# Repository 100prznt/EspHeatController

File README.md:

# HeatController
Bang-bang heat controller with 2 channels. ESP8266 based and compatible with Home Assistant.

## Specs
- ESP8266MOD (ESP-12-F)
- Onboard USB-UART bridge (FTDI)
- 230 VAC power supply with higher isolation voltage (for use in wet environment)
- Automatic switching of the power supply between USB and AC power
- Fully compatible with ESPHome and Home Assistant
- 2 output channels (230 VAC max. 10 A)
- 5 header for DS18B20 1-Wire temperature sensors
- Header for analog input

## Assembly
The PCB fits into a [Spelsberg TG PC 1612-9-to](https://www.spelsberg.de/industrieleergehaeuse/glatt-mit-befestigungsnocken/20100701/) enclosure. There is lots of space for the 230 V wiring in the lower area. I have installed PowerCon sockets from Neutrik here and M8 sockets for the DS818B20 sensors.

## Home Assistant

### Dashboard
The initial use of the __EspHeatController__ for me was as a frost watcher in addition to a pipe heating system. I created a separate dashboard in Home Assistant for this use case.

You can find the configuration for this dashboard here:

* [dashboard/lovelace_ehc_config.yaml](dashboard/lovelace_ehc_config.yaml)

The following HACS extensions are required for this dashboard:

* [Mushroom](https://github.com/piitaya/lovelace-mushroom)
* [UI Card for Better Thermostat](https://github.com/KartoffelToby/better-thermostat-ui-card)

## Usage
As mentioned above, I use the __EspHeatController__ as a frost protector, the ESPHome config [esphome_ehc_config.yaml](esphome_ehc_config.yaml) implements a bang-bang controller for this. Alternatively, the hardware can be configured as a thermostat. It is also possible to control a cooling system in addition to the heater using the two switching channels.

## Function and description

### Datasheets
* [FTDI FT232BL](https://ftdichip.com/wp-content/uploads/2020/08/DS_FT232BL_BQ.pdf)
* [STMicroelectronics LD1117S](http://www.st.com/content/ccc/resource/technical/document/datasheet/99/3b/7d/91/91/51/4b/be/CD00000544.pdf/files/CD00000544.pdf/jcr:content/translations/en.CD00000544.pdf)
* [TI TPS2104](https://www.ti.com/lit/gpn/tps2104)
* [Rohm UMH3N](https://fscdn.rohm.com/en/products/databook/datasheet/discrete/transistor/digital/umh3ntn-e.pdf)
* [AI Thinker ESP8266MOD](https://docs.ai-thinker.com/_media/esp8266/docs/esp-12f_product_specification_en.pdf)

## Hardware Versions
See [versions.md](versions.md) for hardware version details.

### Known bugs in HW rev. v1.0
* [ ] Different resistor packages (R0603 vs. R0805W)
* [ ] IC301 invalide function table for USB power only
* [ ] IC300 (LD1117S) thermal != gnd
* [ ] IC200 (FT232BL) logiclevel for RST pin must be 5 V

### Features for next version
Features for new hardware versions.

* [ ] Onboard temperature sensor
* [ ] X202: Use stadard FTDI header pin assigment ([Datasheet TTL-232R](https://ftdichip.com/wp-content/uploads/2023/07/DS_TTL-232R_CABLES.pdf))
* [ ] Hardware lock between both relays (to use as 2-way motor switch)
* [ ] Hardware lock for the relays in boot state (check an [IO expander](https://esphome.io/#miscellaneous-components))
* [ ] Expand space between PE and GND
* [ ] Testpins for 5 V power supply
* [ ] Change FT232BL to [FT232RNL](https://ftdichip.com/wp-content/uploads/2023/03/DS_FT232RN.pdf) or external programmer

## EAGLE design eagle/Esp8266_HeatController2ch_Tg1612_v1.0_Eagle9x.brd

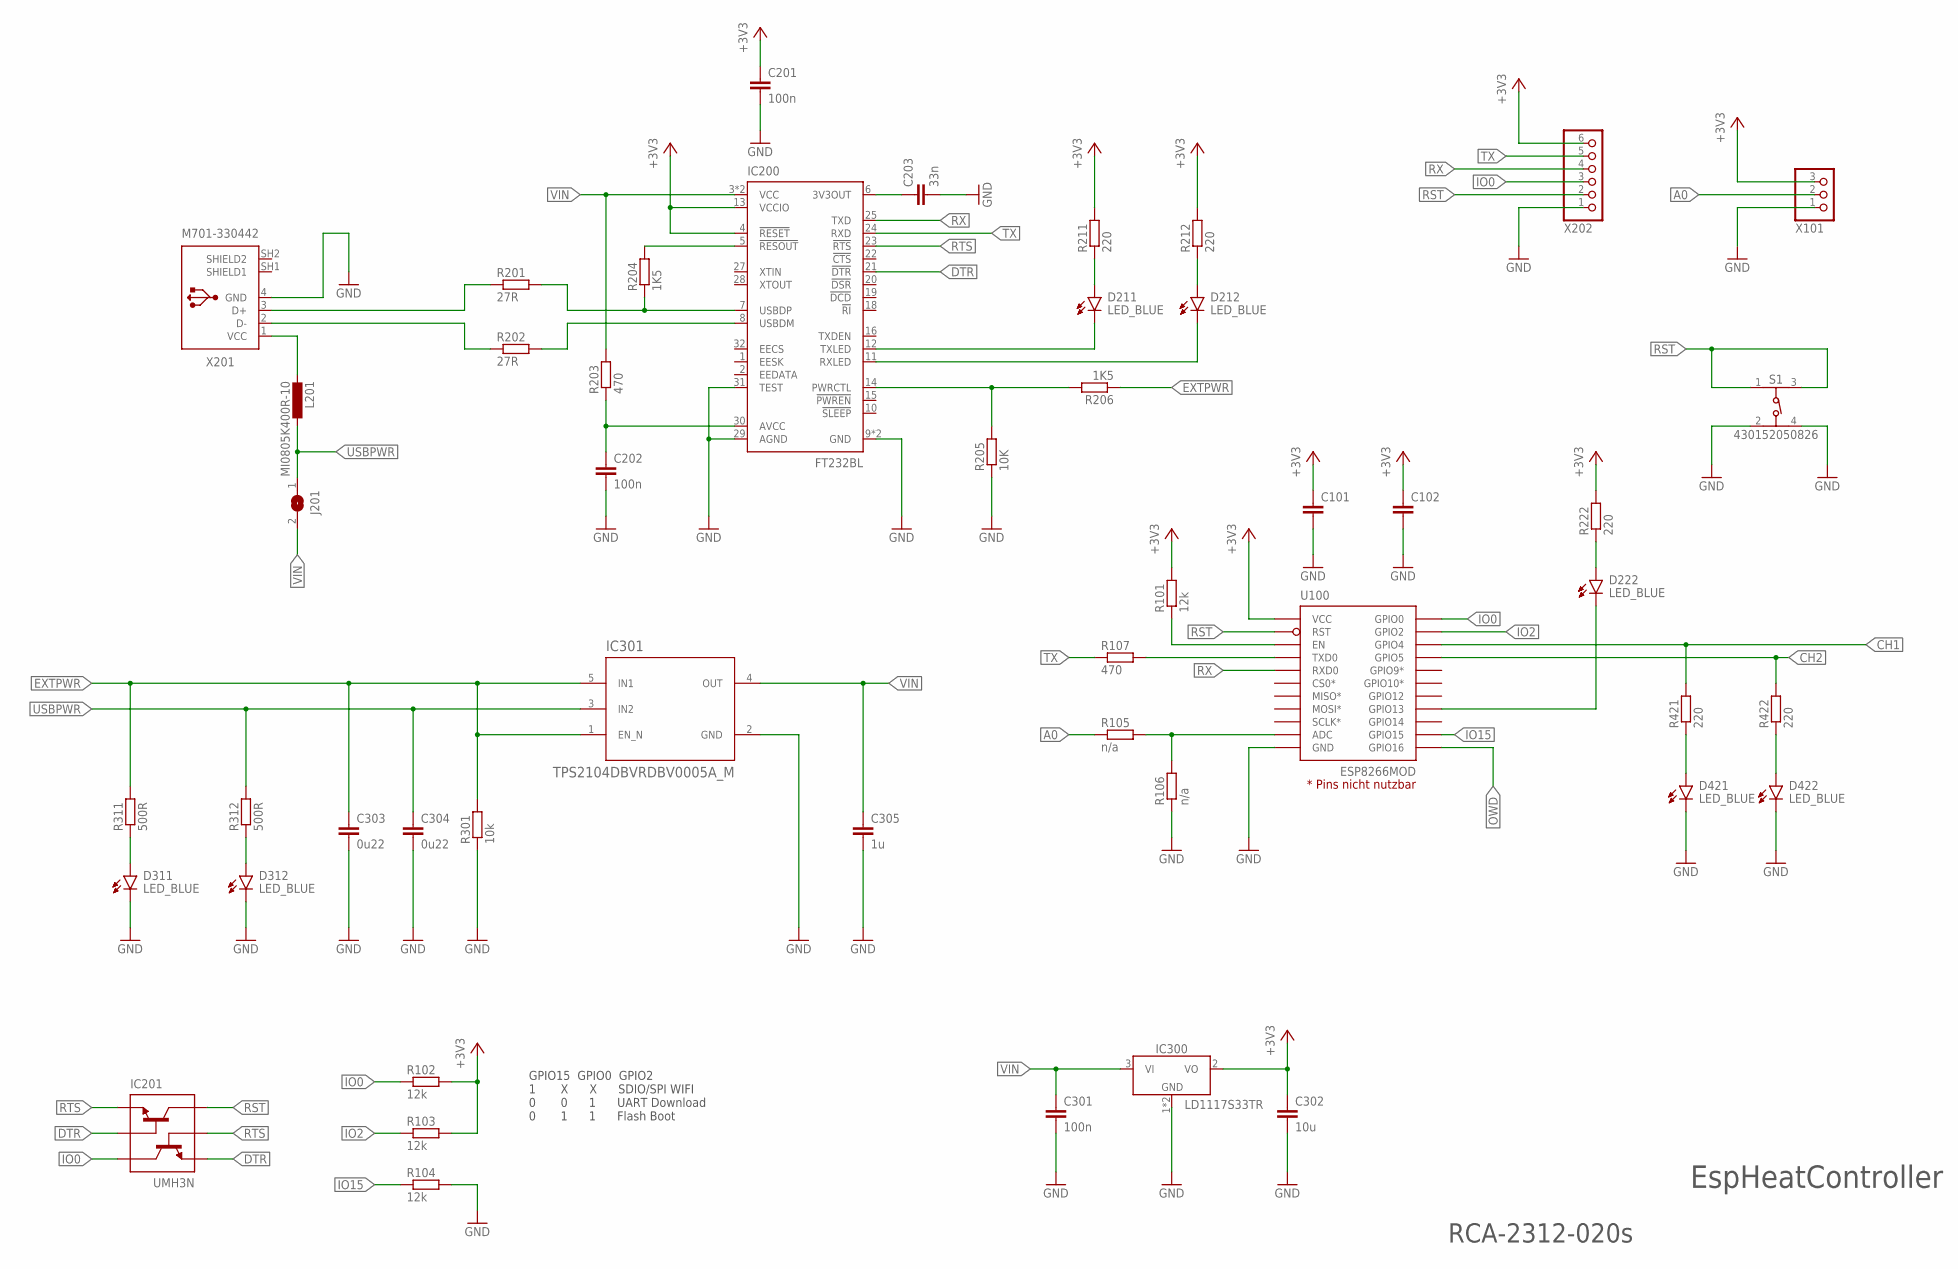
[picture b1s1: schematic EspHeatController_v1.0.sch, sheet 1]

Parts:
C101, C102: C-EUC0805; C0805
C201, C202, C301: 100n; C0805
C203: 33n; C0805
C302: 10u; C0805
C303, C304: 0u22; C0805
C305: 1u; C0805
D211, D212, D222, D311, D312, D421, D422: LED_BLUE; LEDC2012X110N_FLAT-B
IC200: FT232BL; LQFP32-7X7
IC201: UMH3N; SOT-363_ROM
IC300: LD1117S33TR; SOT230P700X170-4
IC301: TPS2104DBVRDBV0005A_M; DBV0005A_M
J201: SJ
L201: MI0805K400R-10; L2012C
R101, R102, R103, R104: 12k; R0603
R105, R106: n/a; R0603
R107, R203: 470; R0603
R201, R202: 27R; R0603
R204, R206: 1K5; R0603
R205: 10K; R0603
R211, R212, R222, R421, R422: 220; R0603
R301: 10k; R0603
R311, R312: 500R; R0603
S1: 430152050826
U100: ESP8266MOD; ESP12F-SMD
X101: PINHD-1X3; 1X03
X201: M701-330442
X202: PINHD-1X6; 1X06

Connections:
+3V3: C101.1, C102.1, C201.1, C302.1, IC200.4 (!RESET), IC200.13 (VCCIO), IC300.2 (VO), R101.2, R102.2, R103.2, R211.2, R212.2, R222.2, U100.VCC, X101.3, X202.6; also elsewhere on the board
A0: R105.1, X101.2
CH1: R421.2, U100.GPIO4; also elsewhere on the board
CH2: R422.2, U100.GPIO5; also elsewhere on the board
DTR: IC200.21 (!DTR), IC201.2 (B1), IC201.4 (E2)
D_N: IC200.8 (USBDM), R202.2
D_P: IC200.7 (USBDP), R201.2, R204.1
EXTPWR: C303.1, IC301.1 (EN_N), IC301.5 (IN1), R206.1, R301.2, R311.2; also elsewhere on the board
GND: C101.2, C102.2, C201.2, C202.2, C203.2, C301.2, C302.2, C303.2, C304.2, C305.2, D311.C, D312.C, D421.C, D422.C, IC200.9 (GND), IC200.17 (GND), IC200.29 (AGND), IC200.31 (TEST), IC300.1 (GND), IC300.4 (GND), IC301.2 (GND), R104.2, R106.1, R205.1, R301.1, S1.2, S1.4, U100.GND, X101.1, X201.4 (GND), X202.1; also elsewhere on the board
IO0: IC201.3 (C2), R102.1, U100.GPIO0, X202.3
IO2: R103.1, U100.GPIO2
IO15: R104.1, U100.GPIO15
unnamed: R105.2, R106.2, U100.ADC
unnamed: R107.2, U100.TXD0
unnamed: R101.1, U100.EN
unnamed: D211.C, IC200.12 (TXLED)
unnamed: C202.1, IC200.30 (AVCC), R203.1
unnamed: D212.C, IC200.11 (RXLED)
unnamed: D211.A, R211.1
unnamed: D212.A, R212.1
unnamed: C203.1, IC200.6 (3V3OUT)
unnamed: D312.A, R312.1
unnamed: D422.A, R422.1
unnamed: L201.2, X201.1 (VCC)
unnamed: D311.A, R311.1
unnamed: D421.A, R421.1
unnamed: IC200.5 (!RESOUT), R204.2
unnamed: IC200.14 (PWRCTL), R205.2, R206.2
unnamed: D222.C, U100.GPIO13
unnamed: D222.A, R222.1
OWD: U100.GPIO16; also elsewhere on the board
RST: IC201.6 (C1), S1.1, S1.3, U100.RST, X202.2
RTS: IC200.23 (!RTS), IC201.1 (E1), IC201.5 (B2)
RX: IC200.25 (TXD), U100.RXD0, X202.4
TX: IC200.24 (RXD), R107.1, X202.5
USBD_N: R202.1, X201.2 (D-)
USBD_P: R201.1, X201.3 (D+)
USBPWR: C304.1, IC301.3 (IN2), J201.1, L201.1, R312.2
VIN: C301.1, C305.1, IC200.3 (VCC), IC200.26 (VCC), IC300.3 (VI), IC301.4 (OUT), J201.2, R203.2

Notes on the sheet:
GPIO15 GPIO0 GPIO2 1 X X SDIO/SPI WIFI 0 0 1 UART Download 0 1 1 Flash Boot
RCA-2312-020s
EspHeatController

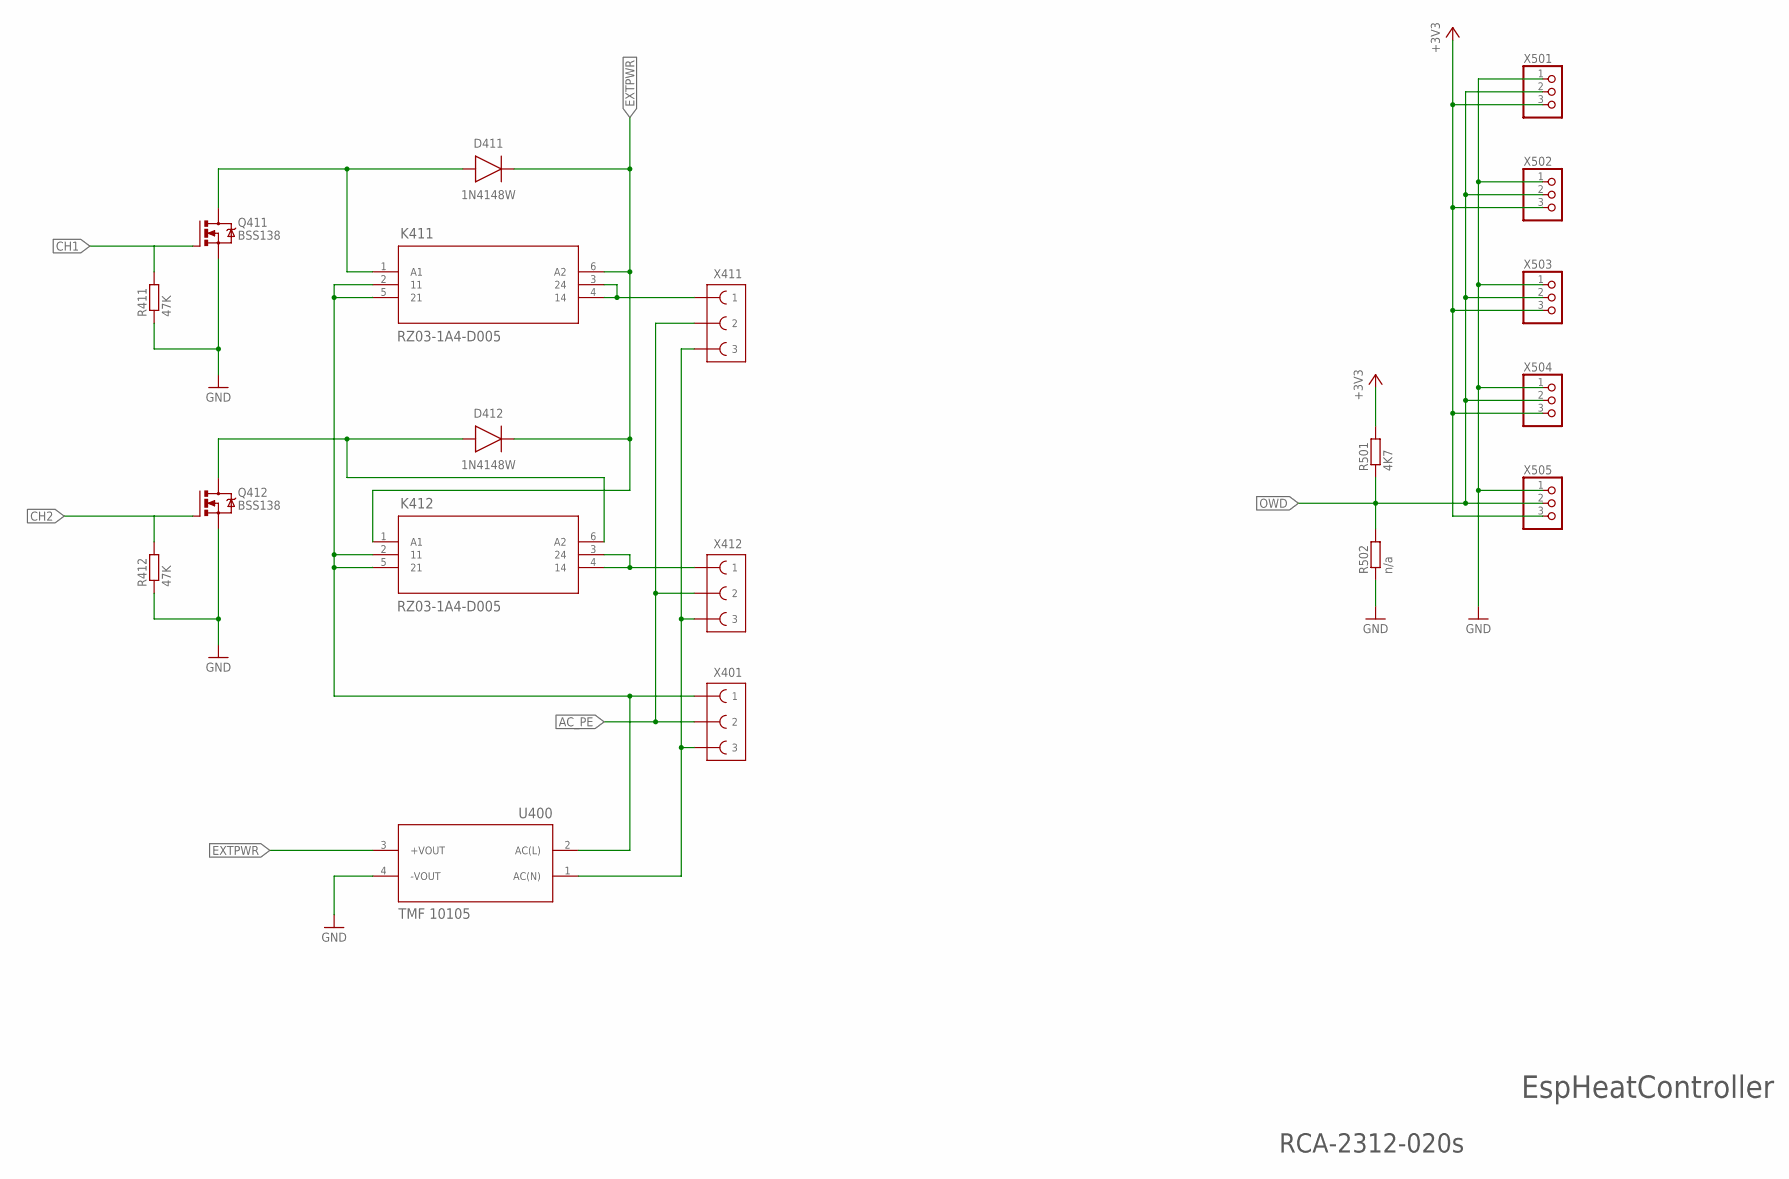
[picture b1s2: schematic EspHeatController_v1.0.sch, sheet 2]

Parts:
D411, D412: 1N4148W; SOD3715X135
K411, K412: RZ03-1A4-D005; RELAY-SPST2_5MM
Q411, Q412: BSS138; SOT23
R411, R412: 47K; R0805W
R501: 4K7; R0805W
R502: n/a; R0805W
U400: TMF 10105; TMF10
X401, X411, X412: SPT2,5/3-V-5,0
X501, X502, X503, X504, X505: PINHD-1X3; 1X03

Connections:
+3V3: R501.2, X501.3, X502.3, X503.3, X504.3, X505.3; also elsewhere on the board
AC_L: K411.2 (11), K411.5 (21), K412.2 (11), K412.5 (21), U400.2 (AC(L)), X401.1A (1), X401.1B (1)
AC_N: U400.1 (AC(N)), X401.3A (3), X401.3B (3), X411.3A (3), X411.3B (3), X412.3A (3), X412.3B (3)
AC_PE: X401.2A (2), X401.2B (2), X411.2A (2), X411.2B (2), X412.2A (2), X412.2B (2)
CH1: Q411.1 (G), R411.2; also elsewhere on the board
CH2: Q412.1 (G), R412.2; also elsewhere on the board
EXTPWR: D411.1 (C), D412.1 (C), K411.6 (A2), K412.1 (A1), U400.3 (+VOUT); also elsewhere on the board
GND: Q411.2 (S), Q412.2 (S), R411.1, R412.1, R502.1, U400.4 (-VOUT), X501.1, X502.1, X503.1, X504.1, X505.1; also elsewhere on the board
unnamed: D412.2 (A), K412.6 (A2), Q412.3 (D)
unnamed: D411.2 (A), K411.1 (A1), Q411.3 (D)
unnamed: K411.3 (24), K411.4 (14), X411.1A (1), X411.1B (1)
unnamed: K412.3 (24), K412.4 (14), X412.1A (1), X412.1B (1)
OWD: R501.1, R502.2, X501.2, X502.2, X503.2, X504.2, X505.2; also elsewhere on the board

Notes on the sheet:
EspHeatController
RCA-2312-020s

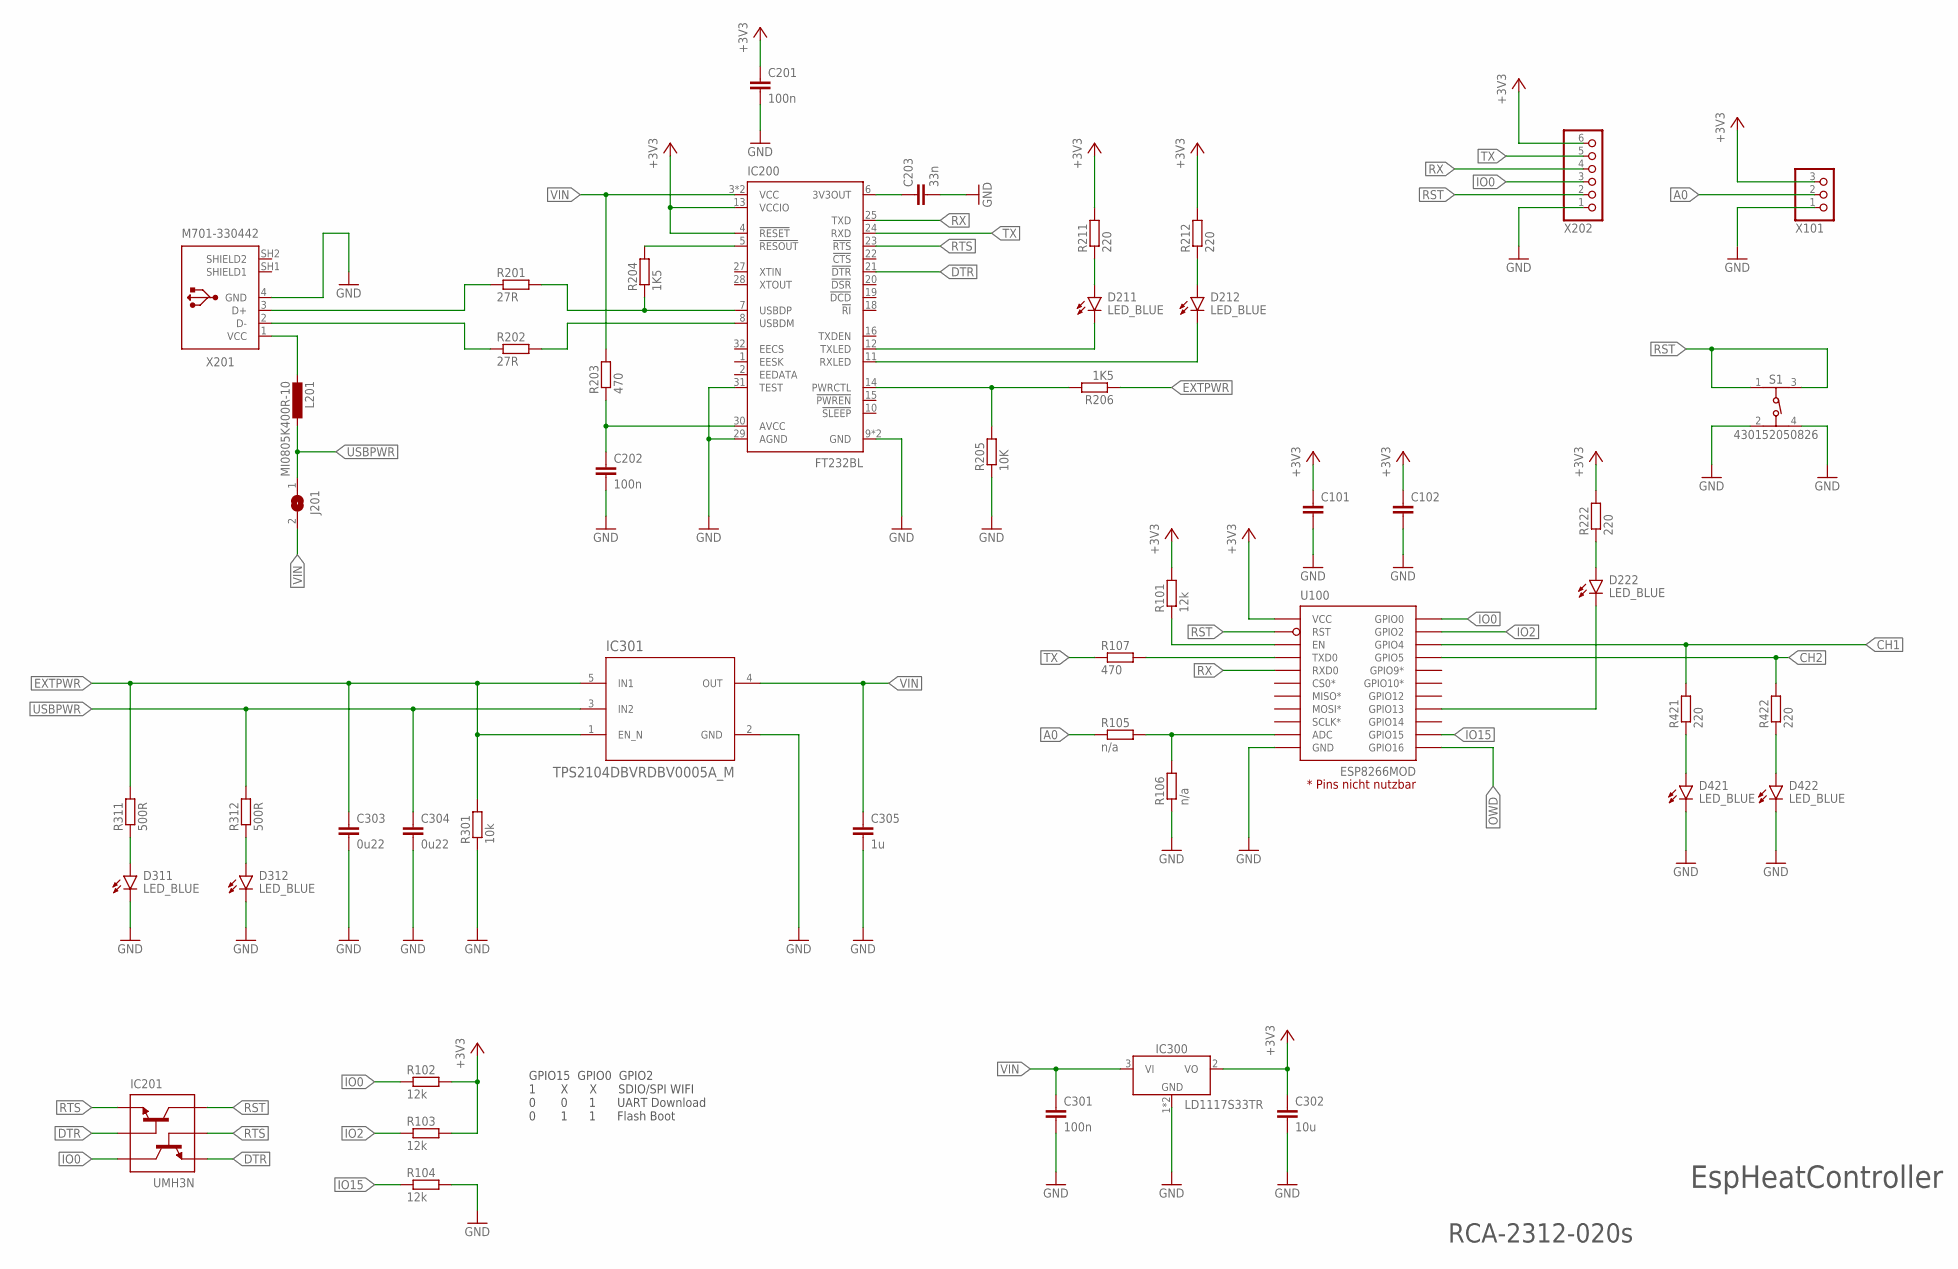
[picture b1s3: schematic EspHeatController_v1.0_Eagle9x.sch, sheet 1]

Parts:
C101, C102: C-EUC0805; C0805
C201, C202, C301: 100n; C0805
C203: 33n; C0805
C302: 10u; C0805
C303, C304: 0u22; C0805
C305: 1u; C0805
D211, D212, D222, D311, D312, D421, D422: LED_BLUE; LEDC2012X110N_FLAT-B
IC200: FT232BL; LQFP32-7X7
IC201: UMH3N; SOT-363_ROM
IC300: LD1117S33TR; SOT230P700X170-4
IC301: TPS2104DBVRDBV0005A_M; DBV0005A_M
J201: SJ
L201: MI0805K400R-10; L2012C
R101, R102, R103, R104: 12k; R0603
R105, R106: n/a; R0603
R107, R203: 470; R0603
R201, R202: 27R; R0603
R204, R206: 1K5; R0603
R205: 10K; R0603
R211, R212, R222, R421, R422: 220; R0603
R301: 10k; R0603
R311, R312: 500R; R0603
S1: 430152050826
U100: ESP8266MOD; ESP12F-SMD
X101: PINHD-1X3; 1X03
X201: M701-330442
X202: PINHD-1X6; 1X06

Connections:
+3V3: C101.1, C102.1, C201.1, C302.1, IC200.4 (!RESET), IC200.13 (VCCIO), IC300.2 (VO), R101.2, R102.2, R103.2, R211.2, R212.2, R222.2, U100.VCC, X101.3, X202.6; also elsewhere on the board
A0: R105.1, X101.2
CH1: R421.2, U100.GPIO4; also elsewhere on the board
CH2: R422.2, U100.GPIO5; also elsewhere on the board
DTR: IC200.21 (!DTR), IC201.2 (B1), IC201.4 (E2)
D_N: IC200.8 (USBDM), R202.2
D_P: IC200.7 (USBDP), R201.2, R204.1
EXTPWR: C303.1, IC301.1 (EN_N), IC301.5 (IN1), R206.1, R301.2, R311.2; also elsewhere on the board
GND: C101.2, C102.2, C201.2, C202.2, C203.2, C301.2, C302.2, C303.2, C304.2, C305.2, D311.C, D312.C, D421.C, D422.C, IC200.9 (GND), IC200.17 (GND), IC200.29 (AGND), IC200.31 (TEST), IC300.1 (GND), IC300.4 (GND), IC301.2 (GND), R104.2, R106.1, R205.1, R301.1, S1.2, S1.4, U100.GND, X101.1, X201.4 (GND), X202.1; also elsewhere on the board
IO0: IC201.3 (C2), R102.1, U100.GPIO0, X202.3
IO2: R103.1, U100.GPIO2
IO15: R104.1, U100.GPIO15
unnamed: R105.2, R106.2, U100.ADC
unnamed: R107.2, U100.TXD0
unnamed: R101.1, U100.EN
unnamed: D211.C, IC200.12 (TXLED)
unnamed: C202.1, IC200.30 (AVCC), R203.1
unnamed: D212.C, IC200.11 (RXLED)
unnamed: D211.A, R211.1
unnamed: D212.A, R212.1
unnamed: C203.1, IC200.6 (3V3OUT)
unnamed: D312.A, R312.1
unnamed: D422.A, R422.1
unnamed: L201.2, X201.1 (VCC)
unnamed: D311.A, R311.1
unnamed: D421.A, R421.1
unnamed: IC200.5 (!RESOUT), R204.2
unnamed: IC200.14 (PWRCTL), R205.2, R206.2
unnamed: D222.C, U100.GPIO13
unnamed: D222.A, R222.1
OWD: U100.GPIO16; also elsewhere on the board
RST: IC201.6 (C1), S1.1, S1.3, U100.RST, X202.2
RTS: IC200.23 (!RTS), IC201.1 (E1), IC201.5 (B2)
RX: IC200.25 (TXD), U100.RXD0, X202.4
TX: IC200.24 (RXD), R107.1, X202.5
USBD_N: R202.1, X201.2 (D-)
USBD_P: R201.1, X201.3 (D+)
USBPWR: C304.1, IC301.3 (IN2), J201.1, L201.1, R312.2
VIN: C301.1, C305.1, IC200.3 (VCC), IC200.26 (VCC), IC300.3 (VI), IC301.4 (OUT), J201.2, R203.2

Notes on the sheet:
GPIO15 GPIO0 GPIO2 1 X X SDIO/SPI WIFI 0 0 1 UART Download 0 1 1 Flash Boot
RCA-2312-020s
EspHeatController

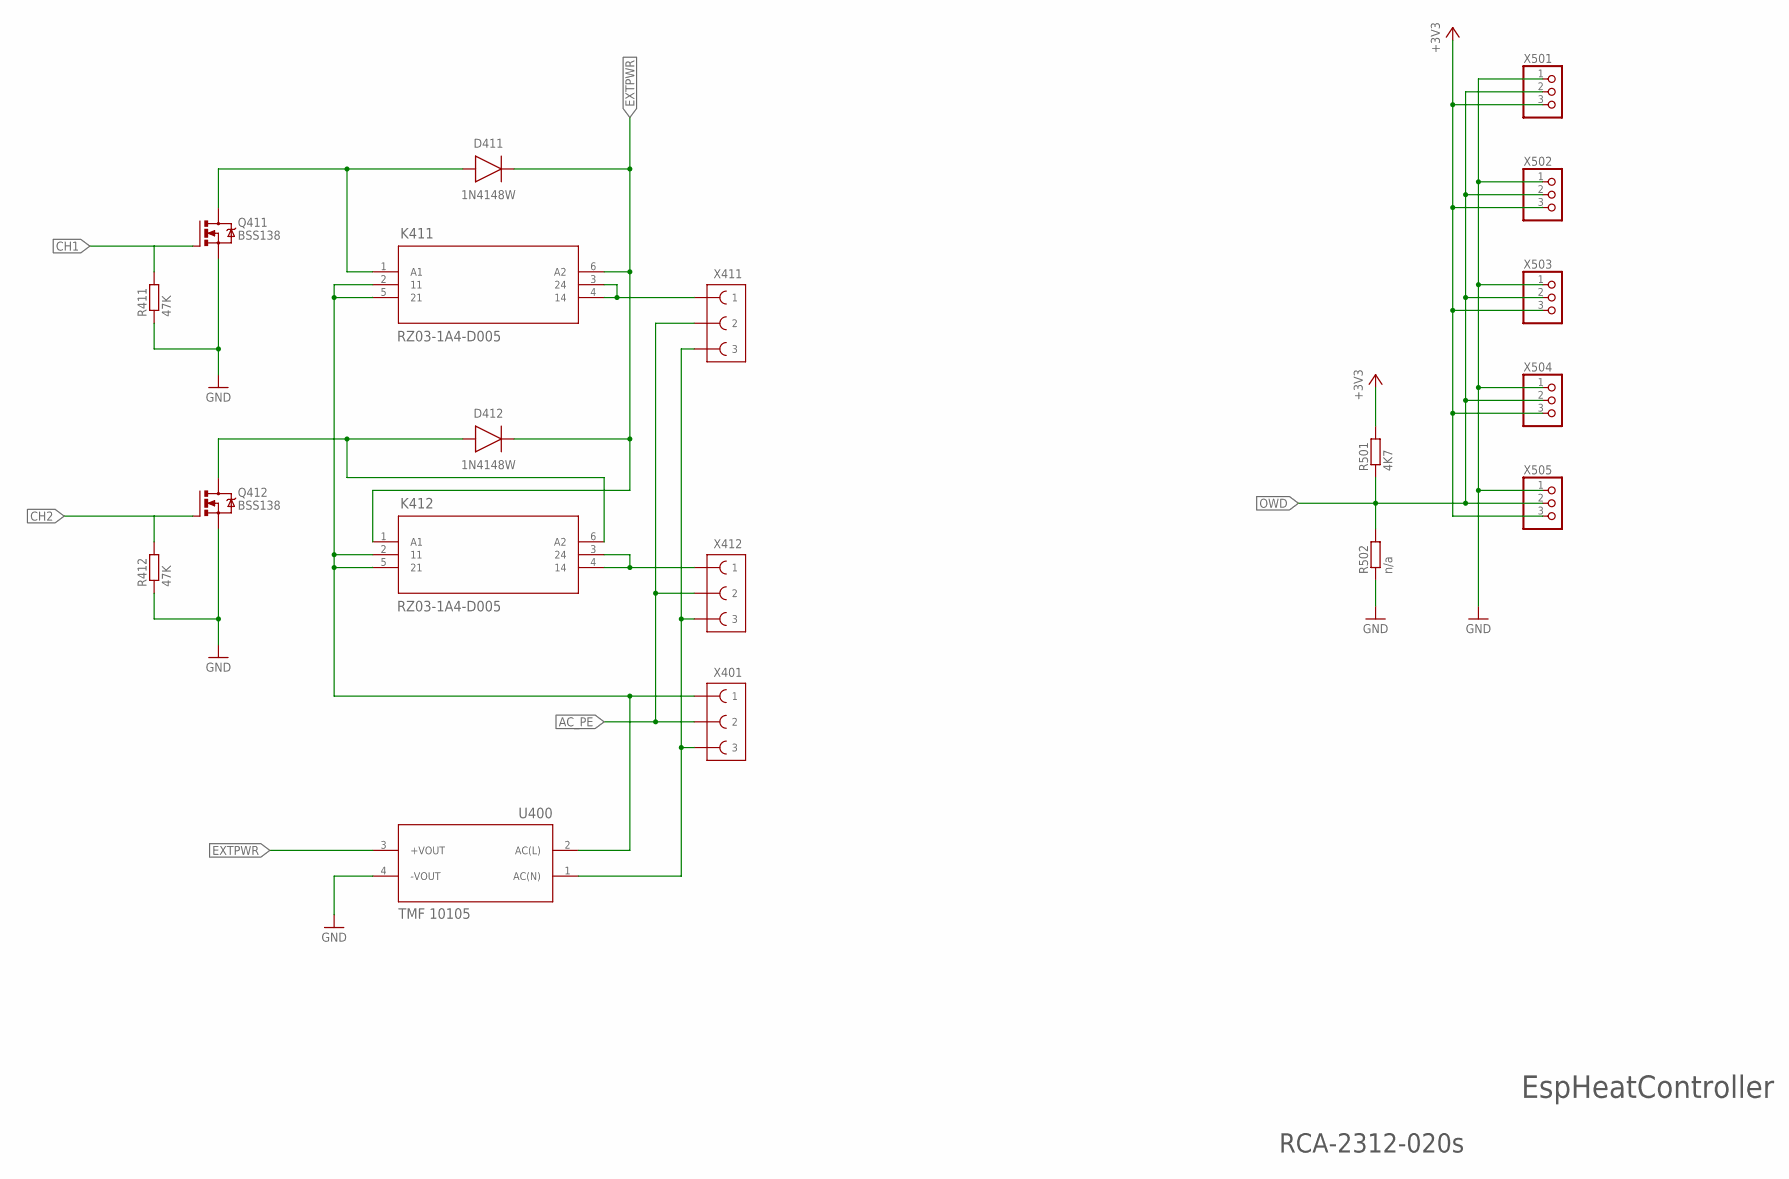
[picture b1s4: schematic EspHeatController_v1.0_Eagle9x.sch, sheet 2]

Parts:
D411, D412: 1N4148W; SOD3715X135
K411, K412: RZ03-1A4-D005; RELAY-SPST2_5MM
Q411, Q412: BSS138; SOT23
R411, R412: 47K; R0805W
R501: 4K7; R0805W
R502: n/a; R0805W
U400: TMF 10105; TMF10
X401, X411, X412: SPT2,5/3-V-5,0
X501, X502, X503, X504, X505: PINHD-1X3; 1X03

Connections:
+3V3: R501.2, X501.3, X502.3, X503.3, X504.3, X505.3; also elsewhere on the board
AC_L: K411.2 (11), K411.5 (21), K412.2 (11), K412.5 (21), U400.2 (AC(L)), X401.1A (1), X401.1B (1)
AC_N: U400.1 (AC(N)), X401.3A (3), X401.3B (3), X411.3A (3), X411.3B (3), X412.3A (3), X412.3B (3)
AC_PE: X401.2A (2), X401.2B (2), X411.2A (2), X411.2B (2), X412.2A (2), X412.2B (2)
CH1: Q411.1 (G), R411.2; also elsewhere on the board
CH2: Q412.1 (G), R412.2; also elsewhere on the board
EXTPWR: D411.1 (C), D412.1 (C), K411.6 (A2), K412.1 (A1), U400.3 (+VOUT); also elsewhere on the board
GND: Q411.2 (S), Q412.2 (S), R411.1, R412.1, R502.1, U400.4 (-VOUT), X501.1, X502.1, X503.1, X504.1, X505.1; also elsewhere on the board
unnamed: D412.2 (A), K412.6 (A2), Q412.3 (D)
unnamed: D411.2 (A), K411.1 (A1), Q411.3 (D)
unnamed: K411.3 (24), K411.4 (14), X411.1A (1), X411.1B (1)
unnamed: K412.3 (24), K412.4 (14), X412.1A (1), X412.1B (1)
OWD: R501.1, R502.2, X501.2, X502.2, X503.2, X504.2, X505.2; also elsewhere on the board

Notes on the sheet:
EspHeatController
RCA-2312-020s

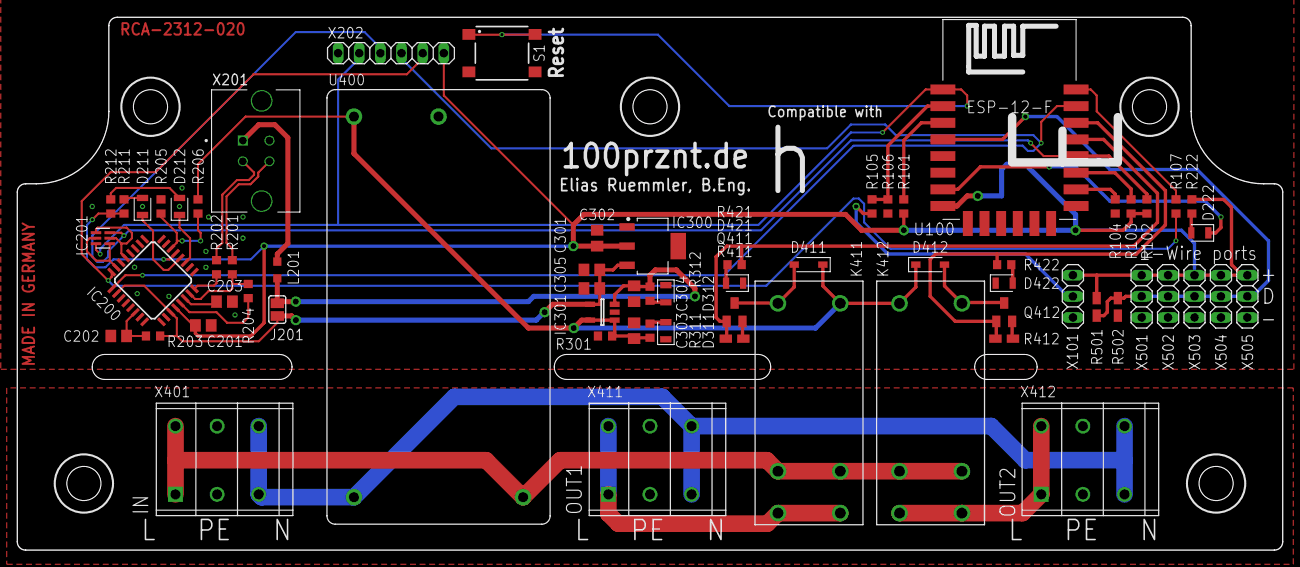
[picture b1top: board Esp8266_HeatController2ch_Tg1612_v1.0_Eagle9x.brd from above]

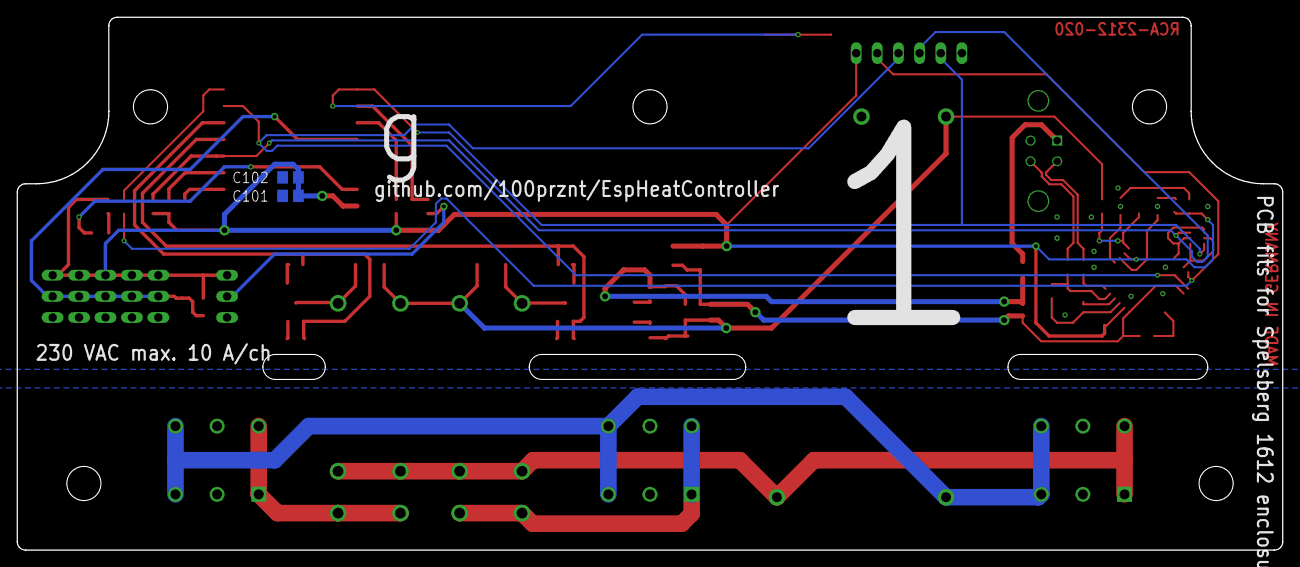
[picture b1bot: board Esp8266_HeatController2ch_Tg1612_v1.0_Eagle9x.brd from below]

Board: 2 copper layers, 152.0 x 64.0 mm, 68 parts (2 on the bottom side), 46 nets.

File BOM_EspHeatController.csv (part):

"Part","Value","Device","Package","Description","STORAGE_RCA","ORDER","CATEGORY","COLOR","DATASHEET-URL","DESCRIPTION.1","MANUFACTURER","MANUFACTURER_PART_NUMBER","MOUSER_PART_NUMBER","RS_PART_NUMBER","FARNELL_PART_NUMBER","SERIES","VALUE.1"
"E001","TG PC 1612-9-to","","","Enclosure","FALSCH","WAHR","","","https://www.spelsberg.de/industrieleergehaeuse/glatt-mit-bef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","","G�nther Spelsberg GmbH + Co. KG","20100701","","","","",
"C101","","C-EUC0805","C0805","CAPACITOR, European symbol","WAHR","","","","","","","","","","","",
"C102","","C-EUC0805","C0805","CAPACITOR, European symbol","WAHR","","","","","","","","","","","",
"C201","100n","C-EUC0805","C0805","CAPACITOR, European symbol","WAHR","","","","","","","","","","","",
"C202","100n","C-EUC0805","C0805","CAPACITOR, European symbol","WAHR","","","","","","","","","","","",
"C203","33n","C-EUC0805","C0805","CAPACITOR, European symbol","WAHR","","","","","","","","","","","",
"C301","100n","C-EUC0805","C0805","CAPACITOR, European symbol","WAHR","","","","","","","","","","","",
"C302","10u","C-EUC0805","C0805","CAPACITOR, European symbol","WAHR","","","","","","","","","","","",
"C303","0u22","C-EUC0805","C0805","CAPACITOR, European symbol","WAHR","","","","","","","","","","","",
"C304","0u22","C-EUC0805","C0805","CAPACITOR, European symbol","WAHR","","","","","","","","","","","",
"C305","1u","C-EUC0805","C0805","CAPACITOR, European symbol","WAHR","","","","","","","","","","","",
"D211","LED_BLUE","CHIP-FLAT-B_0805","LEDC2012X110N_FLAT-B","","FALSCH","WAHR","LED","BLUE","","CHIP LED FLAT","","","","","","","LED_BLUE"
"D212","LED_BLUE","CHIP-FLAT-B_0805","LEDC2012X110N_FLAT-B","","WAHR","","LED","BLUE","","CHIP LED FLAT","","","","","","","LED_BLUE"
"D222","LED_BLUE","CHIP-FLAT-B_0805","LEDC2012X110N_FLAT-B","","WAHR","","LED","BLUE","","CHIP LED FLAT","","","","","","","LED_BLUE"
"D311","LED_BLUE","CHIP-FLAT-B_0805","LEDC2012X110N_FLAT-B","","WAHR","","LED","BLUE","","CHIP LED FLAT","","","","","","","LED_BLUE"
"D312","LED_BLUE","CHIP-FLAT-B_0805","LEDC2012X110N_FLAT-B","","WAHR","","LED","BLUE","","CHIP LED FLAT","","","","","","","LED_BLUE"
"D411","1N4148W","DIODE_1N4148W-7-F_SOD123G","SOD3715X135","Diode Rectifier - Popular parts","FALSCH","WAHR","Diode","","","DIODE GEN PURP 100V 300MA SOD123 ","Diodes Incorporated","","","","2675147","","1N4148W"
"D412","1N4148W","DIODE_1N4148W-7-F_SOD123G","SOD3715X135","Diode Rectifier - Popular parts","FALSCH","WAHR","Diode","","","DIODE GEN PURP 100V 300MA SOD123 ","Diodes Incorporated","","","","2675147","","1N4148W"
"D421","LED_BLUE","CHIP-FLAT-B_0805","LEDC2012X110N_FLAT-B","","WAHR","","LED","BLUE","","CHIP LED FLAT","","","","","","","LED_BLUE"
"D422","LED_BLUE","CHIP-FLAT-B_0805","LEDC2012X110N_FLAT-B","","WAHR","","LED","BLUE","","CHIP LED FLAT","","","","","","","LED_BLUE"
"IC200","FT232BL","FT232BL","LQFP32-7X7","USB to serial UART interface","FALSCH","WAHR","","","","","","FT232BL/TR","","","","",
"IC201","UMH3N","UMH3NTNSOT-363_ROM","SOT-363_ROM","","FALSCH","WAHR","","","","","ROHM Semiconductor","UMH3NTN","","","1680404","",
"IC300","LD1117S33TR","LD1117_SOT223","SOT230P700X170-4","Adjustable and fixed positive voltage regulator","FALSCH","WAHR","IC_Linear","","","Adjustable voltage regulator","STMicroelectronics","LD1117S50TR","","686-9379","","LM1117",
"IC301","TPS2104DBVR","TPS2104DBVRDBV0005A_M","DBV0005A_M","","FALSCH","","","","","TPS2104DBVR ","Texas Instruments","TPS2104DBVR","","","","",
"J201","","SJ","SJ","SMD solder JUMPER","WAHR","","","","","","","","","","","",
"K411","RZ03-1A4-D005","1-1415899-6","RELAY-SPST2_5MM","","FALSCH","WAHR","Power Relays","","","RZ03-1A4-D012","TE Connectivity","1-1415899-6","","","","SCHRACK Power PCB Relay RZ",
"K412","RZ03-1A4-D005","1-1415899-6","RELAY-SPST2_5MM","","FALSCH","WAHR","Power Relays","","","RZ03-1A4-D012","TE Connectivity","1-1415899-6","","","","SCHRACK Power PCB Relay RZ",
"L201","MH2029-400Y","L-EUL2012C","L2012C","INDUCTOR, European symbol","FALSCH","WAHR","","","","MH2029-400Y","Bourns","MH2029-400Y","","","2859028","",
"Q411","BSS138","NMOSFETSOT23-GSD","SOT23","N-Channel MOSFET - Generic","FALSCH","WAHR","Transistor","","","","","","","","2323154","","NMOSFET"
"Q412","BSS138","NMOSFETSOT23-GSD","SOT23","N-Channel MOSFET - Generic","FALSCH","WAHR","Transistor","","","","","","","","","","NMOSFET"
"R101","12k","R-EU_R0603","R0603","RESISTOR, European symbol","WAHR","","","","","","","","","","","",
"R102","12k","R-EU_R0603","R0603","RESISTOR, European symbol","WAHR","","","","","","","","","","","",
"R103","12k","R-EU_R0603","R0603","RESISTOR, European symbol","WAHR","","","","","","","","","","","",
"R104","12k","R-EU_R0603","R0603","RESISTOR, European symbol","WAHR","","","","","","","","","","","",
"R105","n/a","R-EU_R0603","R0603","RESISTOR, European symbol","WAHR","","","","","","","","","","","",
"R106","n/a","R-EU_R0603","R0603","RESISTOR, European symbol","WAHR","","","","","","","","","","","",
"R107","470","R-EU_R0603","R0603","RESISTOR, European symbol","WAHR","","","","","","","","","","","",
"R201","27R","R-EU_R0603","R0603","RESISTOR, European symbol","WAHR","","","","","","","","","","","",
"R202","27R","R-EU_R0603","R0603","RESISTOR, European symbol","WAHR","","","","","","","","","","","",
"R203","470","R-EU_R0603","R0603","RESISTOR, European symbol","WAHR","","","","","","","","","","","",
"R204","1K5","R-EU_R0603","R0603","RESISTOR, European symbol","WAHR","","","","","","","","","","","",
"R205","10K","R-EU_R0603","R0603","RESISTOR, European symbol","WAHR","","","","","","","","","","","",
"R206","1K5","R-EU_R0603","R0603","RESISTOR, European symbol","WAHR","","","","","","","","","","","",
"R211","220","R-EU_R0603","R0603","RESISTOR, European symbol","WAHR","","","","","","","","","","","",
"R212","220","R-EU_R0603","R0603","RESISTOR, European symbol","WAHR","","","","","","","","","","","",
"R222","220","R-EU_R0603","R0603","RESISTOR, European symbol","WAHR","","","","","","","","","","","",
"R301","10k","R-EU_R0603","R0603","RESISTOR, European symbol","WAHR","","","","","","","","","","","",
"R311","500R","R-EU_R0603","R0603","RESISTOR, European symbol","WAHR","","","","","","","","","","","",
"R312","500R","R-EU_R0603","R0603","RESISTOR, European symbol","WAHR","","","","","","","","","","","",
"R411","47K","R-EU_R0805W","R0805W","RESISTOR, European symbol","WAHR","","","","","","","","","","","",
"R412","47K","R-EU_R0805W","R0805W","RESISTOR, European symbol","WAHR","","","","","","","","","","","",
"R421","220","R-EU_R0603","R0603","RESISTOR, European symbol","WAHR","","","","","","","","","","","",
"R422","220","R-EU_R0603","R0603","RESISTOR, European symbol","WAHR","","","","","","","","","","","",
"R501","4K7","R-EU_R0805W","R0805W","RESISTOR, European symbol","WAHR","","","","","","","","","","","",
"R502","n/a","R-EU_R0805W","R0805W","RESISTOR, European symbol","WAHR","","","","","","","","","","","",
"S1","430152050826","430152050826","","WS-TASV SMT Tact Switch 6x6 mm","FALSCH","WAHR","","","https://www.we-online.com/redexpert/spec/430152050826?ae","","","430152050826","","","2065110","","430152050826"
"U100","ESP8266MOD","ESP8266MOD","ESP12F-SMD","","WAHR","","","","","","","","","","","",
"U400","TMF 10105","TMF_101","TMF10","","FALSCH","WAHR","","","","","","","","","2829604","",
"X101","","PINHD-1X3","1X03","PIN HEADER","WAHR","","","","","","","","","","","",
"X201","M701-330442","M701-330442","M701-330442","USB(2.0) Type-B, RCPT, 4POS, THT-VERT","FALSCH","WAHR","Connector","","","CONN RCPT USB2.0 TYPEB 4POS VERT","Harwin","M701-330442","","","2751680","",
"X202","","PINHD-1X6","1X06","PIN HEADER","WAHR","","","","","","","","","","","",
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
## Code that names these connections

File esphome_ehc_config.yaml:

esphome:
  name: heat-controller
  friendly_name: "Heat Controller"

esp8266:
  board: esp12e

# Enable logging
logger:

# Enable Home Assistant API
api:
  encryption:
    key: <your api key>

ota:


wifi:
  ssid: !secret wifi_ssid
  password: !secret wifi_password
  # I feel better with static IPs, delete entry if not desired
  manual_ip:
    static_ip: <device ip>
    gateway: <your gateway>
    subnet: 255.255.255.0

  # Enable fallback hotspot (captive portal) in case wifi connection fails
  ap:
    ssid: "HeatController"
    password: <your password>

captive_portal:

# Status LED
status_led:
  pin:
    number: GPIO13
    inverted: true

# 1-wire config
dallas:
  - pin: GPIO16

# Relais config
switch:
  - platform: gpio
    pin:
      number: GPIO4
    id: heater_relay_1
    name: "Heater Relay CH1"
  - platform: gpio
    pin:
      number: GPIO5
    id: heater_relay_2
    name: "Heater Relay CH2"


sensor:
  - platform: uptime
    name: "HeatController Uptime"
  - platform: wifi_signal
    name: "HeatController WiFi Signal"
    update_interval: 60s
    # DS18B20 sensors
  - platform: dallas
    address: <uid of DS18B20, end with ...aa28>
    id: heater_sensor_1
    name: "Heater Sensor CH1"
  - platform: dallas
    address: <uid of DS18B20, end with ...aa28>
    id: heater_sensor_2
    name: "Heater Sensor CH2"
  # Optional sensors
  - platform: dallas
    address: <uid of DS18B20, end with ...aa28>
    id: environment_sensor
    name: "Environment Sensor"

# Controller
climate:
  - platform: bang_bang
    name: "Controller CH1"
    sensor: heater_sensor_1
    default_target_temperature_low: 20 °C
    default_target_temperature_high: 25 °C
    heat_action:
      - switch.turn_on: heater_relay_1
    idle_action:
      - switch.turn_off: heater_relay_1
  - platform: bang_bang
    name: "Controller CH2"
    sensor: heater_sensor_2
    default_target_temperature_low: 20 °C
    default_target_temperature_high: 25 °C
    heat_action:
      - switch.turn_on: heater_relay_2
    idle_action:
      - switch.turn_off: heater_relay_2

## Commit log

2023-12-11 Add cad renderings
2023-12-11 update rederings
2023-12-11 update renderings
2023-12-12 Add BOM
2023-12-14 Add dashboard
2023-12-14 Add status LED
2023-12-14 update images
2023-12-15 change header image
2023-12-15 rename images
2023-12-15 Add controller status
2023-12-15 Add version info
2023-12-15 update file names
2023-12-16 Add prototype
2023-12-21 Update case rendering
2024-01-11 Add current design
2024-01-11 add datasheets
2024-01-14 rebase

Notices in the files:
parts and their libraries:
RohmSemiconductor: COPYRIGHT: Copyright (C) 2023 Ultra Librarian. All rights reserved.
Relays: COPYRIGHT: Copyright (C) 2016 Accelerated Designs. All rights reserved
Wurth_Switch_WS-TASV: Copyright: Würth Elektronik
